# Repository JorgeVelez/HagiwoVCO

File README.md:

# HAGIWO VCO Eurorack module (PCB edition)

This repo contains a Surface-Mount PCB layout for three modules by [hagiwo](https://www.youtube.com/channel/UCxErrnnVNEAAXPZvQFwobQw) remixed by [luislutz](https://github.com/luislutz/Arduino-VDCO) into a single Eurorack module, that design was iterated by [pansapiens](https://github.com/pansapiens/HAGIWO-Arduino-VDCO), and this repo is all of those things converted to a surface-mount PCB by Crows Electromusic.

This oscillator module is based on Arduino Nano and the Mozzi library.

The module has three modes - Chord generator, Additive synth mode and FM synth mode.

While most of the components are surface mount, some effort has been taken to make it hand-solderable.

## Original work by hagiwo:

- Additive VCO https://note.com/solder_state/n/n30b3a8737b1e
- FM VCO https://note.com/solder_state/n/n88317851a4c7
- Chord VCO https://note.com/solder_state/n/n681d2e07e324
- Check out all hagiwo's videos on youtube. A huge inspiration.

## Modifications by luislutz:

- Combine hagiwo's Additive, FM, and Chord modules into a single module.
- Add CV inputs for parameters 1 and 2.
- Add a VCA gain CV input normalized to 5V, with digital clipping if gain cv is over 5V
- The Sketch uses about 95% of the Memory on an Arduino Nano

### Modifications by pansapiens:

- uses single 5.1V Zener diodes rather than Schottky diodes for over-voltage protection.
- uses a single RGB LED rather than three LEDs.
- uses a momentary button for mode switching (with hardware debouncing)
- make the gain knob accessible on the front panel instead of as a trimpot
- some hacks to use more common resistor values (e.g. 2x1M instead of 1x500k)
- added diodes near the power input for over voltage protection

### Modifications by Crows Electromusic

- [x] convert it to a SMD PCB design
- [x] switch to a TWO LED design (can show four states: off, l-on, r-on, r+l-on)
- [x] switch gain knob back to a trimpot (but make it front-panel accessible via a pinhole) 
- [ ] PCB based panel
- [ ] ?? 

## Build notes

NOTE: the crows version has not been made or validated yet. Build at your own risk.

# Code

## Compiling

To compile the code you need to install the [Mozzi](https://github.com/sensorium/Mozzi) Arduino library and ensure that `#define AUDIO_MODE HIFI` is set in `mozzi_config.h`.

## Flashing

To flash a cheapo Arduino Nano clone, you may need to select "ATmega328P (Old Bootloader)" under Tools->Processor in the Arduino IDE.

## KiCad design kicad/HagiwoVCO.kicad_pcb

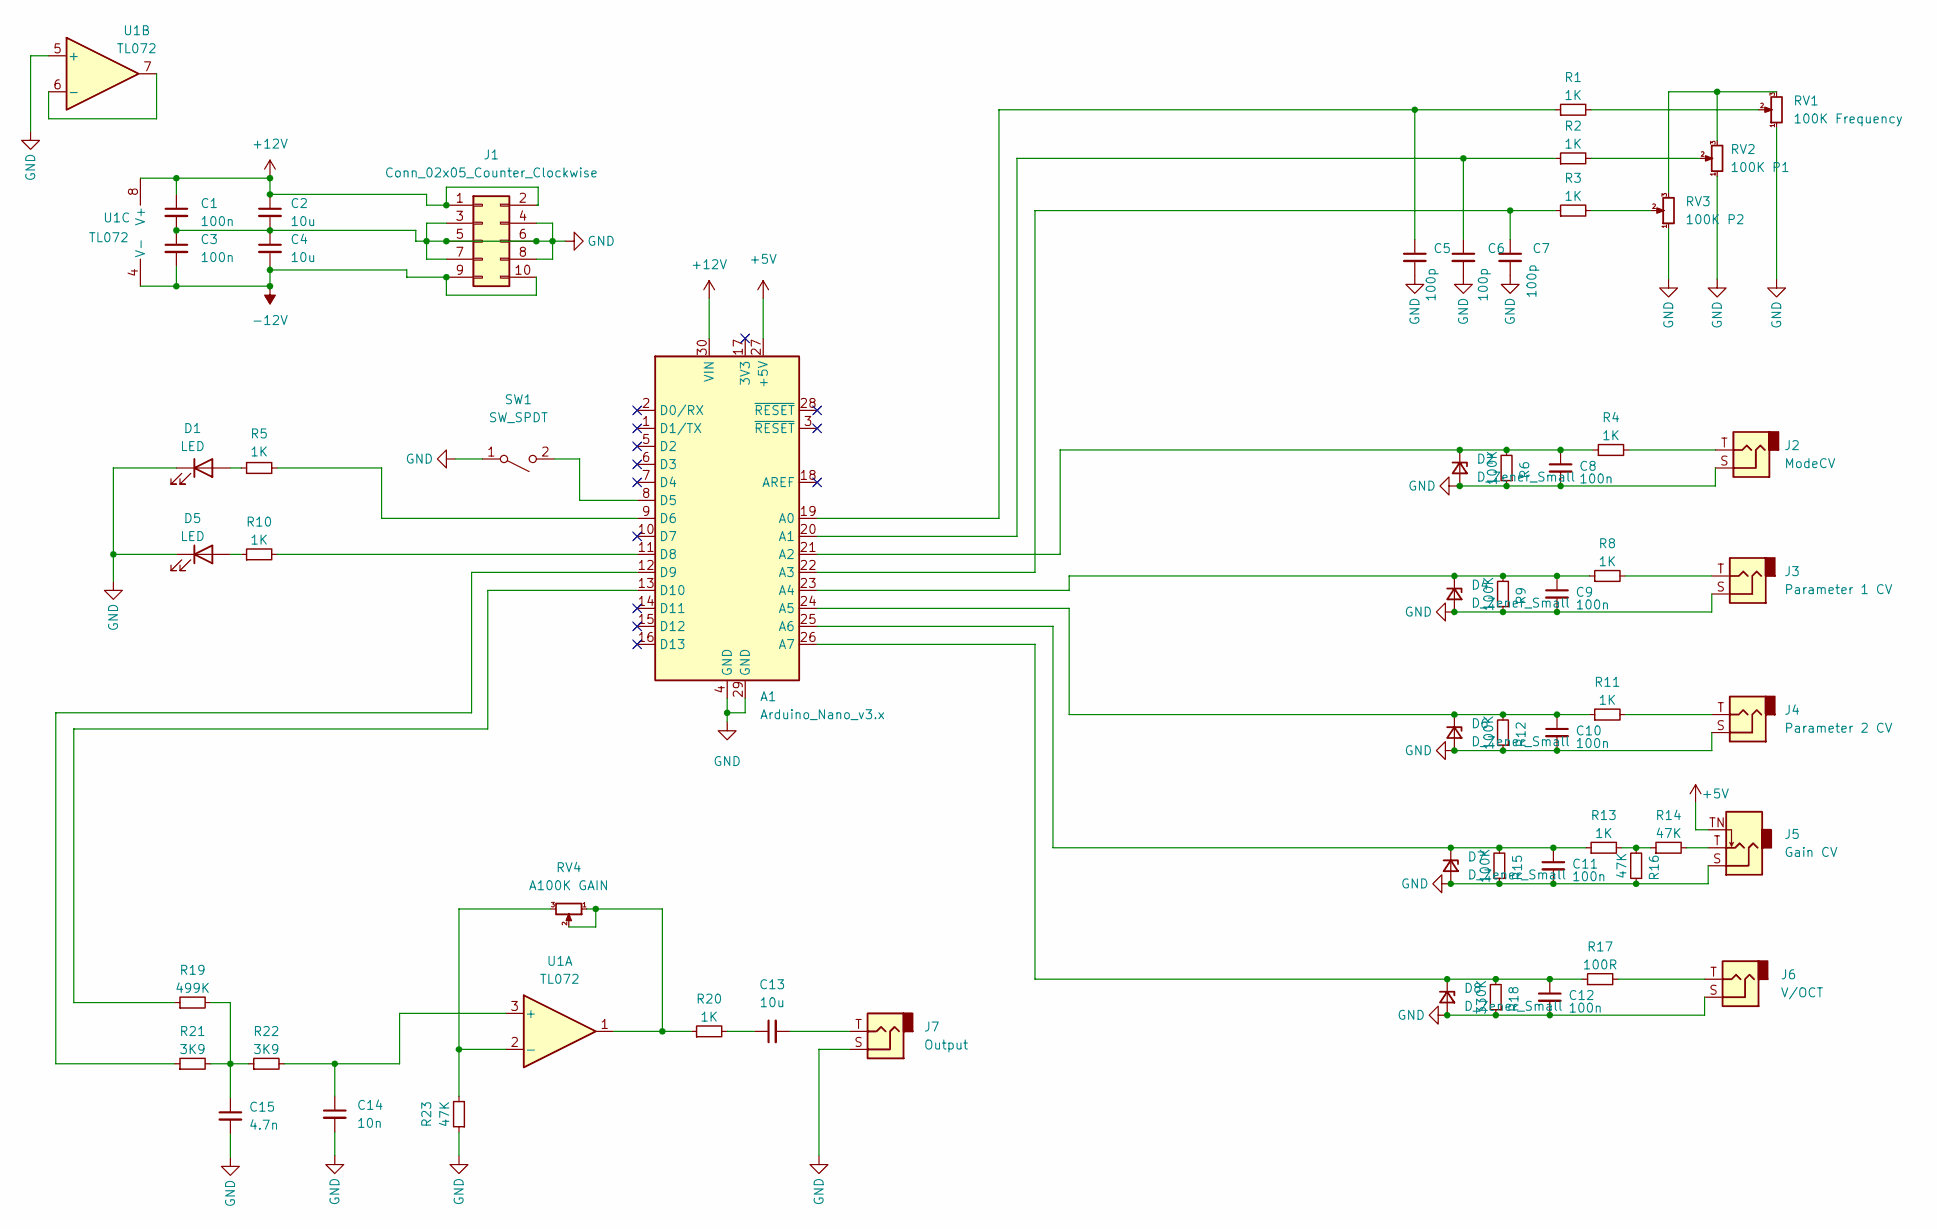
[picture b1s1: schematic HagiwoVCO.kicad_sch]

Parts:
A1: Arduino_Nano_v3.x; Arduino_Nano
C1, C3, C8, C9, C10, C11, C12: 100n; C_0805_2012Metric_Pad1.18x1.45mm_HandSolder
C2, C4, C13: 10u; C_0805_2012Metric_Pad1.18x1.45mm_HandSolder
C5, C6, C7: 100p; C_0805_2012Metric_Pad1.18x1.45mm_HandSolder
C14: 10n; C_0805_2012Metric_Pad1.18x1.45mm_HandSolder
C15: 4.7n; C_0805_2012Metric_Pad1.18x1.45mm_HandSolder
D1, D5: LED; LED_D5.0mm
D2, D4, D6, D7, D8: D_Zener_Small; D_0805_2012Metric_Pad1.15x1.40mm_HandSolder
J1: Conn_02x05_Counter_Clockwise; PinHeader_2x05_P2.54mm_Vertical
J2: ModeCV; Jack_3.5mm_QingPu_WQP-PJ398SM_Vertical_CircularHoles
J3: Parameter 1 CV; Jack_3.5mm_QingPu_WQP-PJ398SM_Vertical_CircularHoles
J4: Parameter 2 CV; Jack_3.5mm_QingPu_WQP-PJ398SM_Vertical_CircularHoles
J5: Gain CV; Jack_3.5mm_QingPu_WQP-PJ398SM_Vertical_CircularHoles
J6: V/OCT; Jack_3.5mm_QingPu_WQP-PJ398SM_Vertical_CircularHoles
J7: Output; Jack_3.5mm_QingPu_WQP-PJ398SM_Vertical_CircularHoles
R1, R2, R3, R4, R5, R8, R10, R11, R13, R20: 1K; R_0805_2012Metric_Pad1.20x1.40mm_HandSolder
R6, R9, R12, R15: 100K; R_0805_2012Metric_Pad1.20x1.40mm_HandSolder
R14, R16, R23: 47K; R_0805_2012Metric_Pad1.20x1.40mm_HandSolder
R17: 100R; R_0805_2012Metric_Pad1.20x1.40mm_HandSolder
R18: 330K; R_0805_2012Metric_Pad1.20x1.40mm_HandSolder
R19: 499K; R_0805_2012Metric_Pad1.20x1.40mm_HandSolder
R21, R22: 3K9; R_0805_2012Metric_Pad1.20x1.40mm_HandSolder
RV1: 100K Frequency; Potentiometer_Alps_RK09L_Single_Vertical
RV2: 100K P1; Potentiometer_Alps_RK09L_Single_Vertical
RV3: 100K P2; Potentiometer_Alps_RK09L_Single_Vertical
RV4: A100K GAIN; Potentiometer_Alps_RK09L_Single_Vertical
SW1: SW_SPDT; SW_PUSH_6mm_H5mm
U1: TL072; DIP-8_W7.62mm

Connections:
+5V: A1.27 (+5V), J5.TN
+12V: A1.30 (VIN), C1.1, C2.1, J1.1, J1.2, U1.8 (V+)
-12V: C3.2, C4.2, J1.9, J1.10, U1.4 (V-)
GND: A1.4 (GND), A1.29 (GND), C1.2, C2.2, C3.1, C4.1, C5.2, C6.2, C7.2, C8.2, C9.2, C10.2, C11.2, C12.2, C14.2, C15.2, D1.1 (K), D2.2 (A), D4.2 (A), D5.1 (K), D6.2 (A), D7.2 (A), D8.2 (A), J1.3, J1.4, J1.5, J1.6, J1.7, J1.8, J2.S, J3.S, J4.S, J5.S, J6.S, J7.S, R6.1, R9.1, R12.1, R15.1, R16.1, R18.1, R23.1, RV1.1, RV2.1, RV3.1, SW1.1 (A), U1.5 (+)
unnamed: A1.8 (D5), SW1.2 (B)
unnamed: A1.9 (D6), R5.2
unnamed: A1.11 (D8), R10.2
unnamed: A1.12 (D9), R21.1
unnamed: A1.13 (D10), R19.1
unnamed: A1.19 (A0), C5.1, R1.1
unnamed: A1.20 (A1), C6.1, R2.1
unnamed: A1.21 (A2), C8.1, D2.1 (K), R4.1, R6.2
unnamed: A1.22 (A3), C7.1, R3.1
unnamed: A1.23 (A4), C9.1, D4.1 (K), R8.1, R9.2
unnamed: A1.24 (A5), C10.1, D6.1 (K), R11.1, R12.2
unnamed: A1.25 (A6), C11.1, D7.1 (K), R13.1, R15.2
unnamed: A1.26 (A7), C12.1, D8.1 (K), R17.1, R18.2
unnamed: C13.1, R20.2
unnamed: C13.2, J7.T
unnamed: C14.1, R22.2, U1.3 (+)
unnamed: C15.1, R19.2, R21.2, R22.1
unnamed: D1.2 (A), R5.1
unnamed: D5.2 (A), R10.1
unnamed: J2.T, R4.2
unnamed: J3.T, R8.2
unnamed: J4.T, R11.2
unnamed: J5.T, R14.2
unnamed: J6.T, R17.2
unnamed: R1.2, RV1.2
unnamed: R2.2, RV2.2
unnamed: R3.2, RV3.2
unnamed: R13.2, R14.1, R16.2
unnamed: R20.1, RV4.1, RV4.2, U1.1
unnamed: R23.2, RV4.3, U1.2 (-)
unnamed: RV1.3, RV2.3, RV3.3
unnamed: U1.6 (-), U1.7

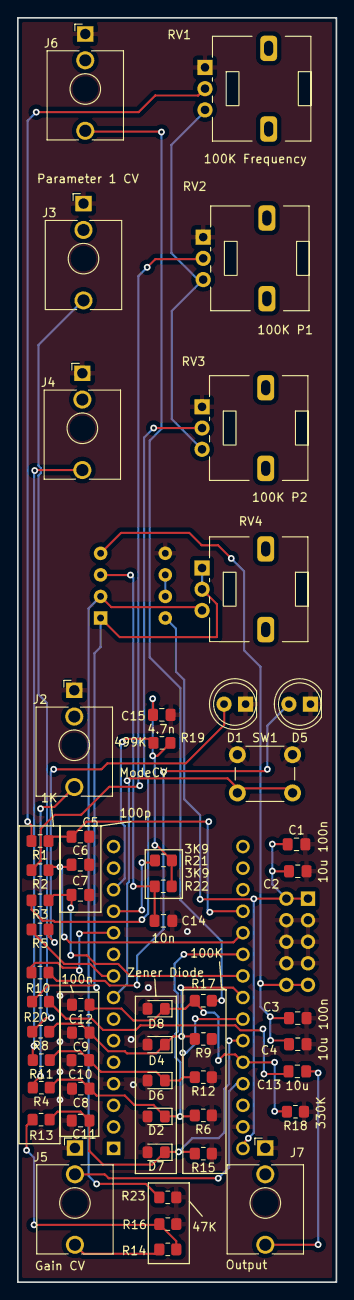
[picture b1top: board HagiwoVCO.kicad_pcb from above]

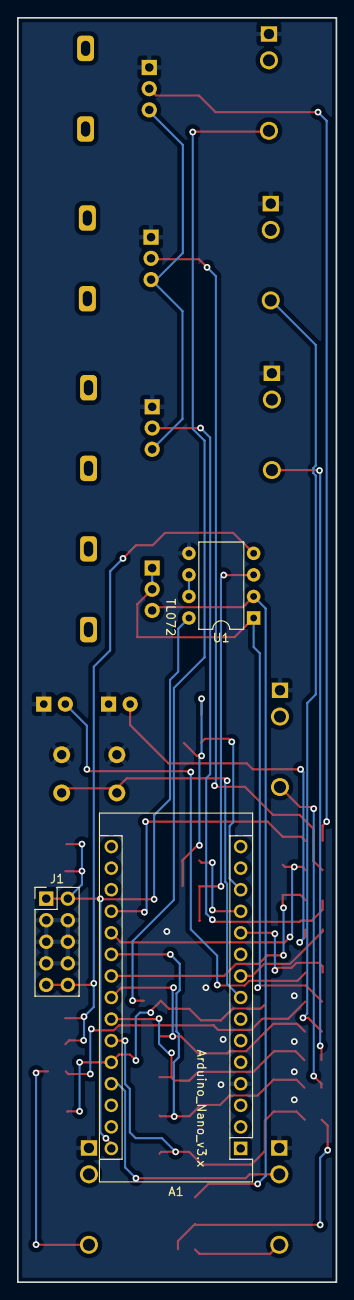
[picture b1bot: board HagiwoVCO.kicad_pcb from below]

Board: 2 copper layers, 37.5 x 148.9 mm, 58 parts (3 on the bottom side), 36 nets.

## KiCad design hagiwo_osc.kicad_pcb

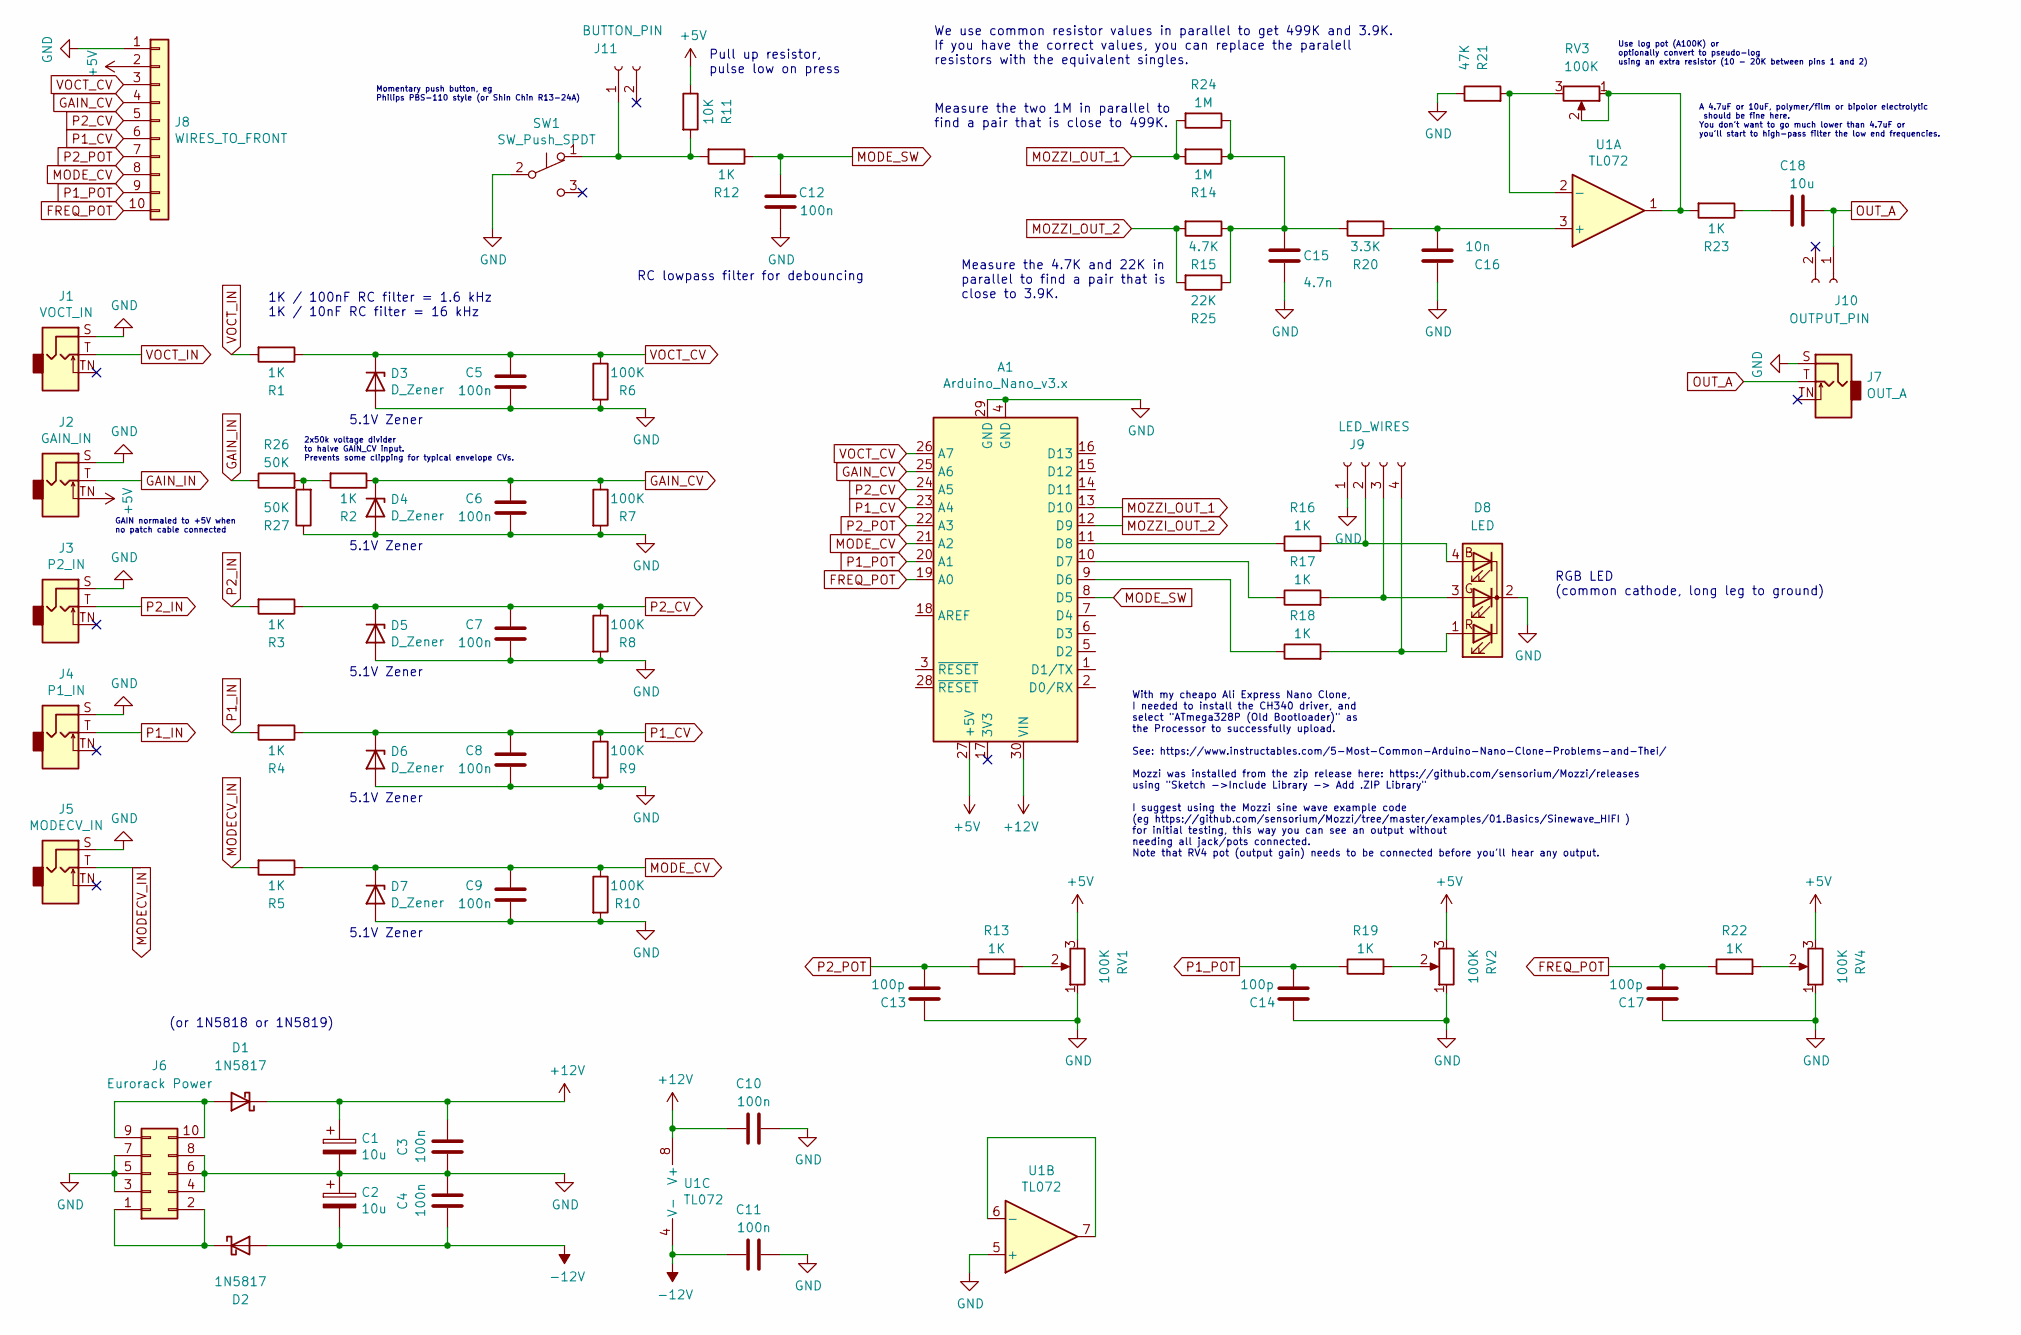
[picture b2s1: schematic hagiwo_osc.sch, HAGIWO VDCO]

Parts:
A1: Arduino_Nano_v3.x; Arduino_Nano
C1, C2: 10u; CP_Radial_D5.0mm_P2.50mm
C3, C4, C5, C6, C7, C8, C9, C11, C12: 100n; R_Axial_DIN0204_L3.6mm_D1.6mm_P2.54mm_Vertical
C10: 100n; R_Axial_DIN0204_L3.6mm_D1.6mm_P5.08mm_Horizontal
C13, C14, C17: 100p; R_Axial_DIN0204_L3.6mm_D1.6mm_P2.54mm_Vertical
C15: 4.7n; R_Axial_DIN0204_L3.6mm_D1.6mm_P2.54mm_Vertical
C16: 10n; R_Axial_DIN0204_L3.6mm_D1.6mm_P2.54mm_Vertical
C18: 10u; R_Axial_DIN0204_L3.6mm_D1.6mm_P2.54mm_Vertical
D1, D2: 1N5817; D_DO-35_SOD27_P2.54mm_Vertical_AnodeUp
D3, D4, D5, D6, D7: D_Zener; D_DO-35_SOD27_P2.54mm_Vertical_AnodeUp
D8: LED; LED_D5.0mm-4_RGB_Wide_Pins
J1: VOCT_IN; 3.5mm_tip_switch_thonkiconn
J2: GAIN_IN; 3.5mm_tip_switch_thonkiconn
J3: P2_IN; 3.5mm_tip_switch_thonkiconn
J4: P1_IN; 3.5mm_tip_switch_thonkiconn
J5: MODECV_IN; 3.5mm_tip_switch_thonkiconn
J6: Eurorack Power; IDC-Header_2x05_P2.54mm_Vertical
J7: OUT_A; 3.5mm_tip_switch_thonkiconn
J8: WIRES_TO_FRONT; PinHeader_1x10_P2.54mm_Vertical
J9: LED_WIRES; PinHeader_1x04_P2.54mm_Vertical
J10: OUTPUT_PIN; PinHeader_1x02_P2.54mm_Vertical
J11: BUTTON_PIN; PinHeader_1x02_P2.54mm_Vertical
R1, R2, R3, R4, R5, R12, R13, R16, R17, R18, R19, R22, R23: 1K; R_Axial_DIN0204_L3.6mm_D1.6mm_P2.54mm_Vertical
R6, R7, R8, R9, R10: 100K; R_Axial_DIN0204_L3.6mm_D1.6mm_P2.54mm_Vertical
R11: 10K; R_Axial_DIN0204_L3.6mm_D1.6mm_P2.54mm_Vertical
R14, R24: 1M; R_Axial_DIN0204_L3.6mm_D1.6mm_P2.54mm_Vertical
R15: 4.7K; R_Axial_DIN0204_L3.6mm_D1.6mm_P2.54mm_Vertical
R20: 3.3K; R_Axial_DIN0204_L3.6mm_D1.6mm_P2.54mm_Vertical
R21: 47K; R_Axial_DIN0204_L3.6mm_D1.6mm_P2.54mm_Vertical
R25: 22K; R_Axial_DIN0204_L3.6mm_D1.6mm_P2.54mm_Vertical
R26, R27: 50K; R_Axial_DIN0204_L3.6mm_D1.6mm_P2.54mm_Vertical
RV1, RV2, RV3, RV4: 100K; Potentiometer_Thonk_Alpha_9mm_Vertical_NoAntirotation
SW1: SW_Push_SPDT; SW_CW_GPTS203211B
U1: TL072; DIP-8_W7.62mm_LongPads

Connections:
+5V: A1.27 (+5V), J2.TN, J8.2, R11.1, RV1.3, RV2.3, RV4.3
+12V: A1.30 (VIN), C1.1, C3.2, C10.1, D1.1 (K), U1.8 (V+)
-12V: C2.2, C4.1, C11.1, D2.2 (A), U1.4 (V-)
FREQ_POT: A1.19 (A0), C17.1, J8.10, R22.1
GAIN_CV: A1.25 (A6), C6.2, D4.1 (K), J8.4, R2.1, R7.1
GAIN_IN: J2.T, R26.1
GND: A1.4 (GND), A1.29 (GND), C1.2, C2.1, C3.1, C4.2, C5.1, C6.1, C7.1, C8.1, C9.1, C10.2, C11.2, C12.1, C13.2, C14.2, C15.2, C16.2, C17.2, D3.2 (A), D4.2 (A), D5.2 (A), D6.2 (A), D7.2 (A), D8.2 (K), J1.S, J2.S, J3.S, J4.S, J5.S, J6.3, J6.4, J6.5, J6.6, J6.7, J6.8, J7.S, J8.1, J9.1, R6.2, R7.2, R8.2, R9.2, R10.2, R21.1, R27.1, RV1.1, RV2.1, RV4.1, SW1.2 (B), U1.5 (+)
MODECV_IN: J5.T, R5.2
MODE_CV: A1.21 (A2), C9.2, D7.1 (K), J8.8, R5.1, R10.1
MODE_SW: A1.8 (D5), C12.2, R12.1
MOZZI_OUT_1: A1.13 (D10), R14.2, R24.2
MOZZI_OUT_2: A1.12 (D9), R15.2, R25.2
unnamed: A1.9 (D6), R18.1
unnamed: A1.10 (D7), R17.1
unnamed: A1.11 (D8), R16.1
unnamed: C15.1, R14.1, R15.1, R20.2, R24.1, R25.1
unnamed: C16.1, R20.1, U1.3 (+)
unnamed: C18.1, R23.1
unnamed: D1.2 (A), J6.9, J6.10
unnamed: D2.1 (K), J6.1, J6.2
unnamed: D8.1 (RA), J9.4, R18.2
unnamed: D8.3 (GA), J9.3, R17.2
unnamed: D8.4 (BA), J9.2, R16.2
unnamed: J11.1, R11.2, R12.2, SW1.1 (A)
unnamed: R2.2, R26.2, R27.2
unnamed: R13.2, RV1.2
unnamed: R19.2, RV2.2
unnamed: R21.2, RV3.3, U1.2 (-)
unnamed: R22.2, RV4.2
unnamed: R23.2, RV3.1, RV3.2, U1.1
unnamed: U1.6 (-), U1.7
OUT_A: C18.2, J7.T, J10.1
P1_CV: A1.23 (A4), C8.2, D6.1 (K), J8.6, R4.1, R9.1
P1_IN: J4.T, R4.2
P1_POT: A1.20 (A1), C14.1, J8.9, R19.1
P2_CV: A1.24 (A5), C7.2, D5.1 (K), J8.5, R3.1, R8.1
P2_IN: J3.T, R3.2
P2_POT: A1.22 (A3), C13.1, J8.7, R13.1
VOCT_CV: A1.26 (A7), C5.2, D3.1 (K), J8.3, R1.1, R6.1
VOCT_IN: J1.T, R1.2

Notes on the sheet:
(or 1N5818 or 1N5819)
RGB LED (common cathode, long leg to ground)
1K / 100nF RC filter = 1.6 kHz 1K / 10nF RC filter = 16 kHz
5.1V Zener
Pull up resistor, pulse low on press
RC lowpass filter for debouncing
Measure the two 1M in parallel to find a pair that is close to 499K.
Measure the 4.7K and 22K in parallel to find a pair that is close to 3.9K.
We use common resistor values in parallel to get 499K and 3.9K. If you have the correct values, you can replace the paralell resistors with the equivalent singles.
With my cheapo Ali Express Nano Clone, I needed to install the CH340 driver, and select "ATmega328P (Old Bootloader)" as the Processor to successfully upload. See: https://www.instructables.com/5-Most-Common-Arduino-Nano-Clone-Problems-and-Thei/ Mozzi was installed from the zip release here: https: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
A 4.7uF or 10uF, polymer/film or bipolor electrolytic should be fine here. You don't want to go much lower than 4.7uF or you'll start to high-pass filter the low end frequencies.
Use log pot (A100K) or optionally convert to pseudo-log using an extra resistor (10 - 20K between pins 1 and 2)
2x50k voltage divider to halve GAIN_CV input. Prevents some clipping for typical envelope CVs.
GAIN normaled to +5V when no patch cable connected
Momentary push button, eg Philips PBS-110 style (or Shin Chin R13-24A)

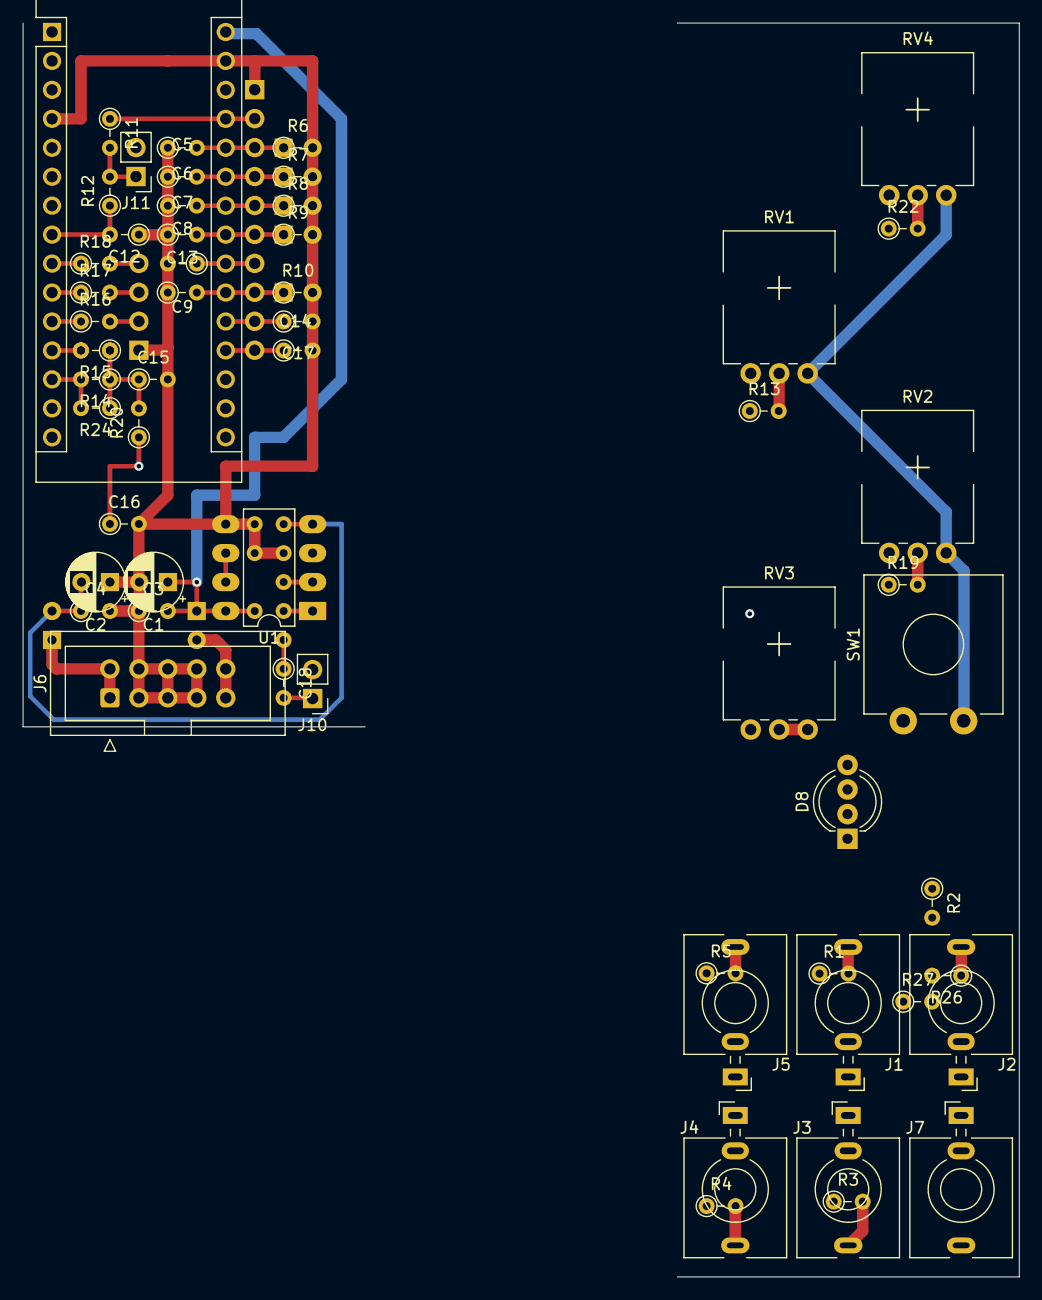
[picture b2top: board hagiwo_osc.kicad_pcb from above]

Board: 4 copper layers, 87.4 x 110.0 mm, 71 parts (0 on the bottom side), 40 nets.

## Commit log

2021-08-29 Add my version with 3D printable front panel, some hardware changes.
2021-08-29 Fix images in README
2021-09-05 Add voltage divider on GAIN_CV since we really need this to prevent clipping.
2022-01-26 Fix link formatting in README
2022-07-06 add kicad project
2022-07-06 couple changes
2022-07-06 Edited readme
2022-07-06 nuked unused files
2022-07-06 first complete routing of smd board
2022-07-06 Update README.md
    iterate on readme, clarify the origin story
2022-07-06 Update README.md
    Added details about my changes
2022-07-07 remove one led, tighten up routing
2022-07-07 the D in DCO isn't adding anything useful
2022-07-07 Renamed project files
2022-09-15 tweak layout
2022-09-27 routing and layout work on pcb
